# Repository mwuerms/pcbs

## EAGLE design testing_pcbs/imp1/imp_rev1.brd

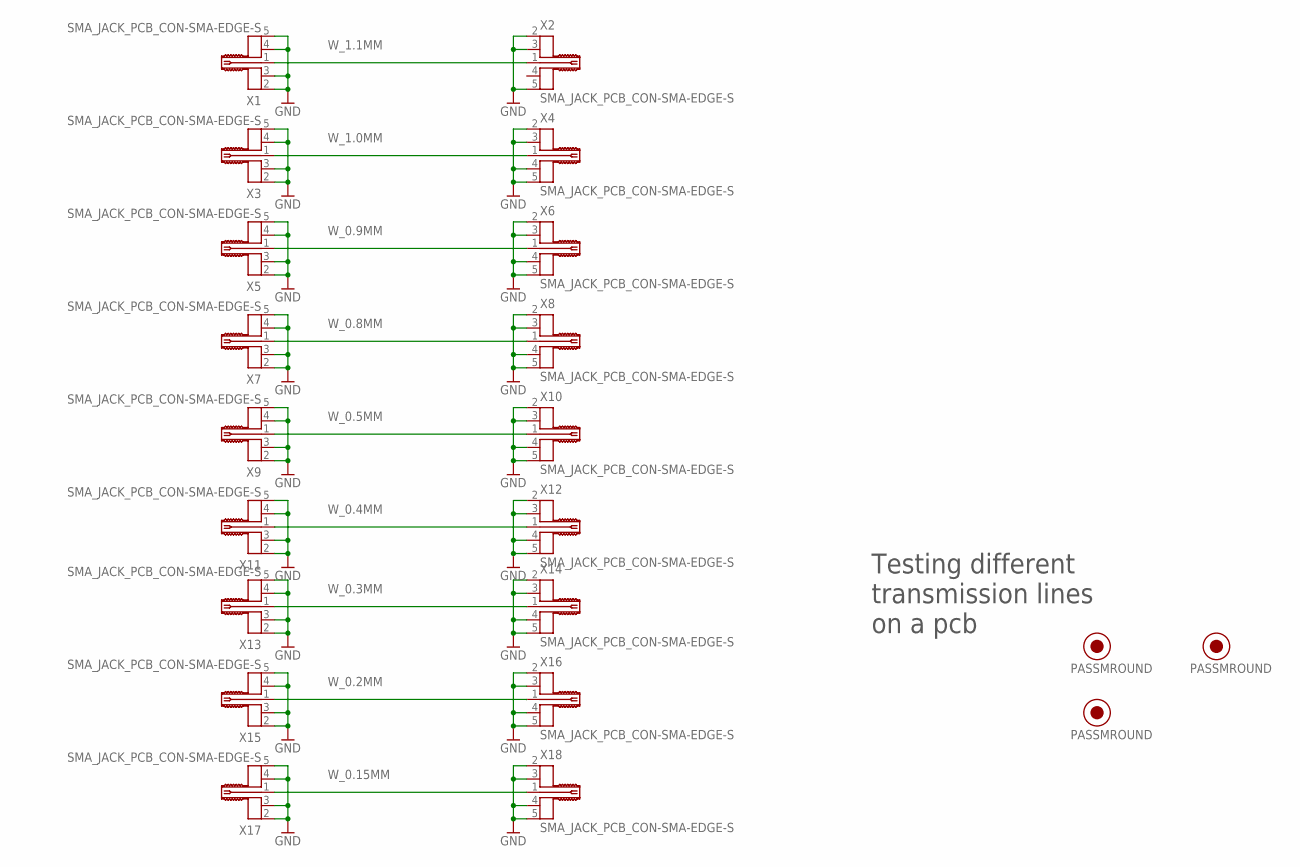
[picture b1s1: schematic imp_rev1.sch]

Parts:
P1, P2, P3: PASSMROUND; PASSM
X1, X2, X3, X4, X5, X6, X7, X8, X9, X10, X11, X12, X13, X14, X15, X16, X17, X18: SMA_JACK_PCB_CON-SMA-EDGE-S

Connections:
GND: X1.2 (GND1), X1.3 (GND2), X1.4 (GND3), X1.5 (GND4), X2.2 (GND1), X2.3 (GND2), X2.5 (GND4), X3.2 (GND1), X3.3 (GND2), X3.4 (GND3), X3.5 (GND4), X4.2 (GND1), X4.3 (GND2), X4.4 (GND3), X4.5 (GND4), X5.2 (GND1), X5.3 (GND2), X5.4 (GND3), X5.5 (GND4), X6.2 (GND1), X6.3 (GND2), X6.4 (GND3), X6.5 (GND4), X7.2 (GND1), X7.3 (GND2), X7.4 (GND3), X7.5 (GND4), X8.2 (GND1), X8.3 (GND2), X8.4 (GND3), X8.5 (GND4), X9.2 (GND1), X9.3 (GND2), X9.4 (GND3), X9.5 (GND4), X10.2 (GND1), X10.3 (GND2), X10.4 (GND3), X10.5 (GND4), X11.2 (GND1), X11.3 (GND2), X11.4 (GND3), X11.5 (GND4), X12.2 (GND1), X12.3 (GND2), X12.4 (GND3), X12.5 (GND4), X13.2 (GND1), X13.3 (GND2), X13.4 (GND3), X13.5 (GND4), X14.2 (GND1), X14.3 (GND2), X14.4 (GND3), X14.5 (GND4), X15.2 (GND1), X15.3 (GND2), X15.4 (GND3), X15.5 (GND4), X16.2 (GND1), X16.3 (GND2), X16.4 (GND3), X16.5 (GND4), X17.2 (GND1), X17.3 (GND2), X17.4 (GND3), X17.5 (GND4), X18.2 (GND1), X18.3 (GND2), X18.4 (GND3), X18.5 (GND4)
W_0.2MM: X15.1, X16.1
W_0.3MM: X13.1, X14.1
W_0.4MM: X11.1, X12.1
W_0.5MM: X9.1, X10.1
W_0.8MM: X7.1, X8.1
W_0.9MM: X5.1, X6.1
W_0.15MM: X17.1, X18.1
W_1.0MM: X3.1, X4.1
W_1.1MM: X1.1, X2.1

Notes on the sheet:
Testing different transmission lines on a pcb

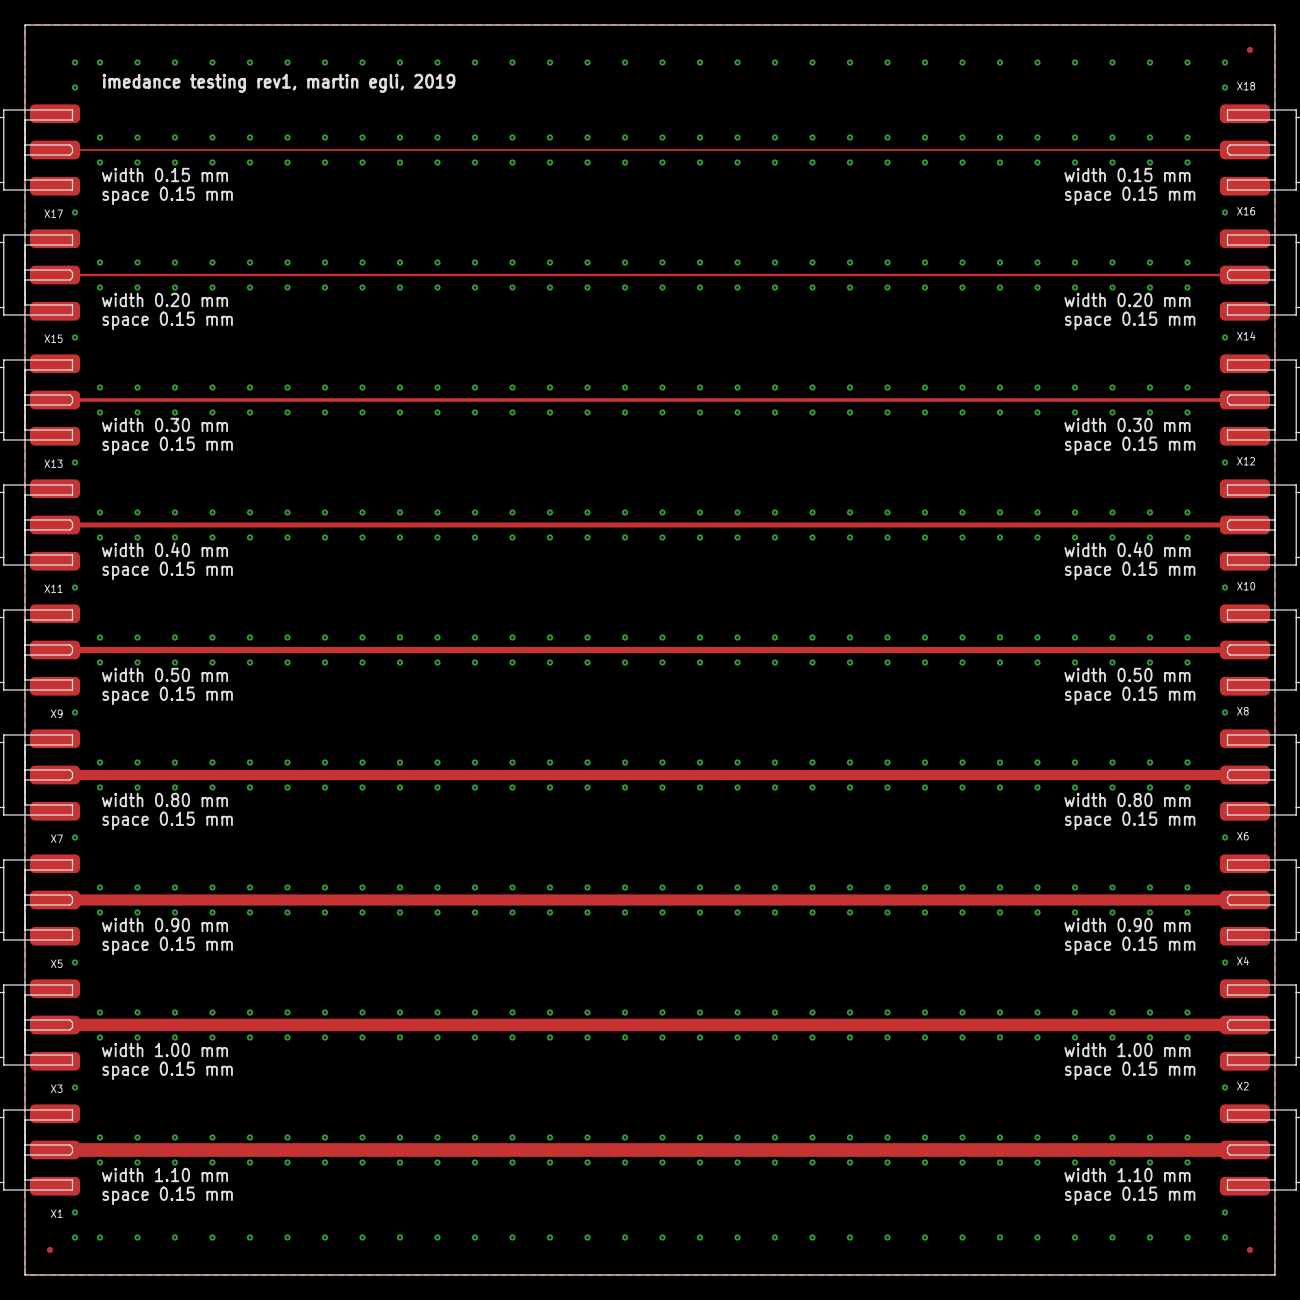
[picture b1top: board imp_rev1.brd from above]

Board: 2 copper layers, 100.0 x 100.0 mm, 21 parts (0 on the bottom side), 10 nets.

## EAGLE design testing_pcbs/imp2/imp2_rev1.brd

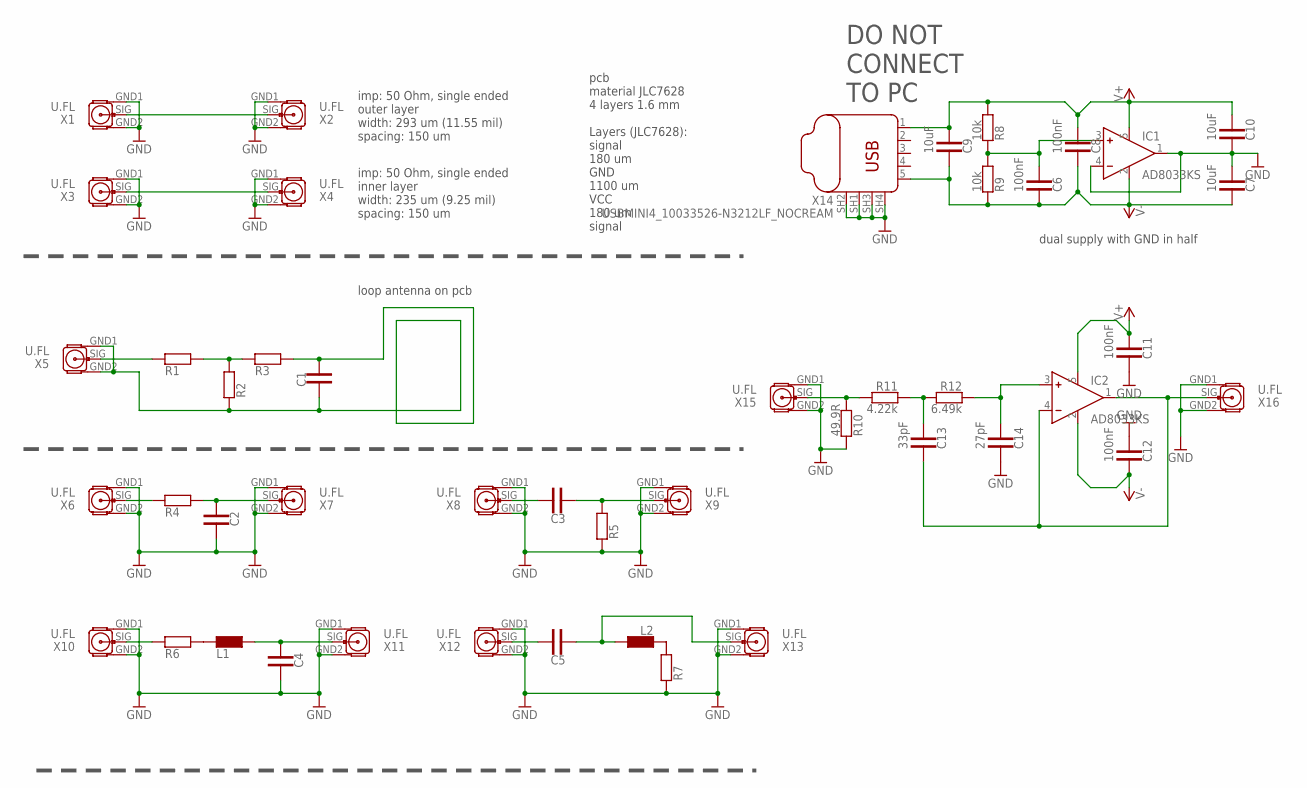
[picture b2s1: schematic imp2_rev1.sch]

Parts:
C1, C2, C3, C4, C5: C0603; 0603MIL
C6, C8, C11, C12: 100nF; 0603MIL
C7, C9, C10: 10uF; 0805MIL
C13: 33pF; 0603MIL
C14: 27pF; 0603MIL
IC1, IC2: AD8033KS; SC-705
L1, L2: L0603; 0603MIL
R1, R2, R3, R4, R5, R6, R7: R0603; 0603MIL
R8, R9: 10k; 0603MIL
R10: 49.9R; 0603MIL
R11: 4.22k; 0603MIL
R12: 6.49k; 0603MIL
X1, X2, X3, X4, X5, X6, X7, X8, X9, X10, X11, X12, X13, X15, X16: U.FL; U.FL_CONUFL001-SMD
X14: USBMINI4_10033526-N3212LF_NOCREAM; USB-MINI_SMD_10033526_NOCREAM

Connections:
GND: C2.1, C4.1, C7.2, C10.1, C11.1, C12.2, C14.1, IC1.1 (OUT), IC1.4 (IN-), R5.1, R7.1, R10.1, X1.GND1, X1.GND2, X2.GND1, X2.GND2, X3.GND1, X3.GND2, X4.GND1, X4.GND2, X6.GND1, X6.GND2, X7.GND1, X7.GND2, X8.GND1, X8.GND2, X9.GND1, X9.GND2, X10.GND1, X10.GND2, X11.GND1, X11.GND2, X12.GND1, X12.GND2, X13.GND1, X13.GND2, X14.SH1 (G1), X14.SH2 (G2), X14.SH3 (G3), X14.SH4 (G4), X15.GND1, X15.GND2, X16.GND1, X16.GND2
unnamed: R1.1, X5.SIG
unnamed: R1.2, R2.2, R3.1
unnamed: R4.1, X6.SIG
unnamed: C2.2, R4.2, X7.SIG
unnamed: C3.1, X8.SIG
unnamed: C3.2, R5.2, X9.SIG
unnamed: R6.1, X10.SIG
unnamed: C4.2, L1.2, X11.SIG
unnamed: C5.1, X12.SIG
unnamed: L1.1, R6.2
unnamed: L2.1, R7.2
unnamed: C5.2, L2.2, X13.SIG
unnamed: C6.2, IC1.3 (IN+), R8.1, R9.2
unnamed: C1.1, C1.2, R2.1, R3.2, X5.GND1, X5.GND2
unnamed: R10.2, R11.2, X15.SIG
unnamed: C13.2, R11.1, R12.2
unnamed: C14.2, IC2.3 (IN+), R12.1
unnamed: C13.1, IC2.1 (OUT), IC2.4 (IN-), X16.SIG
V+: C8.2, C9.2, C10.2, C11.2, IC1.5 (VDD), IC2.5 (VDD), R8.2, X14.1 (VBUS)
V-: C6.1, C7.1, C8.1, C9.1, C12.1, IC1.2 (VSS), IC2.2 (VSS), R9.1, X14.5 (GND)
W_0.235MM_LAY2: X3.SIG, X4.SIG
W_0.293MM_TOP: X1.SIG, X2.SIG

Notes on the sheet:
imp: 50 Ohm, single ended outer layer width: 293 um (11.55 mil) spacing: 150 um
pcb material JLC7628 4 layers 1.6 mm Layers (JLC7628): signal 180 um GND 1100 um VCC 180 um signal
imp: 50 Ohm, single ended inner layer width: 235 um (9.25 mil) spacing: 150 um
loop antenna on pcb
dual supply with GND in half
DO NOT CONNECT TO PC

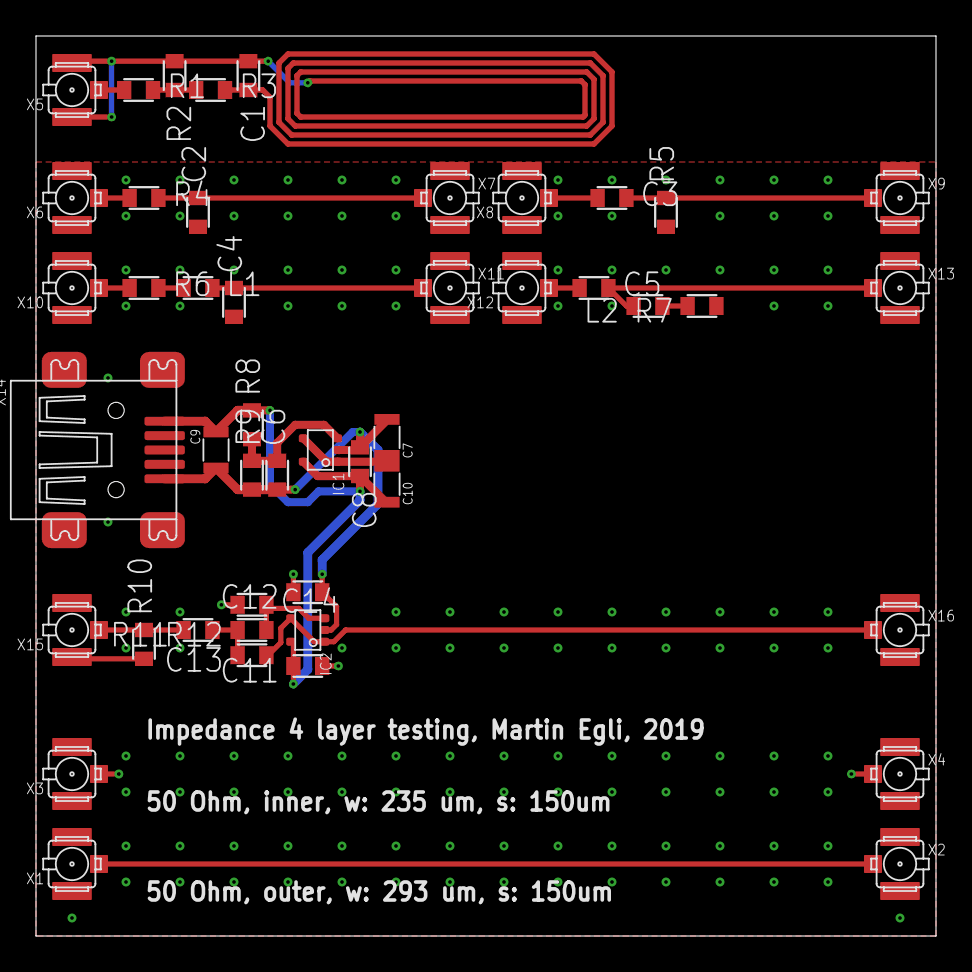
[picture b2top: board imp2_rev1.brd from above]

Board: 4 copper layers, 50.0 x 50.0 mm, 46 parts (0 on the bottom side), 23 nets.

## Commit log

2019-10-08 pcbs: added testing pcbs imp1 (impedance measurement) and imp2 with some more tests
2019-11-21 bluepill pinout added
